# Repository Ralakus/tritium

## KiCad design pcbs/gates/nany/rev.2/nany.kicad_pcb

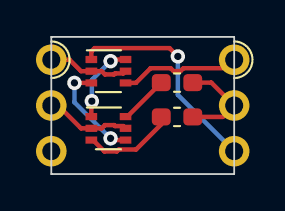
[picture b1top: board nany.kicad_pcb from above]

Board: 2 copper layers, 10.2 x 7.6 mm, 6 parts (0 on the bottom side), 9 nets.

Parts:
J1, J2: Conn_01x03; Edge_Castellation_1x03_P2.54
Q1, Q2: BSS8402DW; SOT-363_SC-70-6
R1, R2: 12k; R_0603_1608Metric_Pad1.05x0.95mm_HandSolder

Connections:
A: J1.1, Q1.2, Q1.5
B: J1.2, Q2.2, Q2.5
unnamed: Q1.3, Q2.4
unnamed: Q1.6, Q2.1
unnamed: Q2.3, R1.1
unnamed: Q2.6, R2.2
Out: J2.2, R1.2, R2.1
Vdd: J2.1, Q1.4
Vss: J2.3, Q1.1

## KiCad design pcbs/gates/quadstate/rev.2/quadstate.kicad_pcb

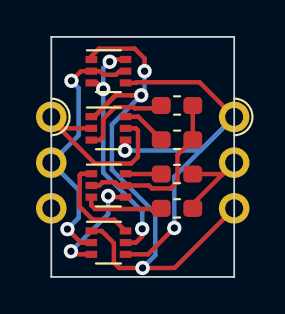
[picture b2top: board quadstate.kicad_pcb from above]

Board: 2 copper layers, 10.2 x 13.3 mm, 10 parts (0 on the bottom side), 13 nets.

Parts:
J1, J2: Conn_01x03; Edge_Castellation_1x03_P2.54
Q1, Q2, Q3, Q4: BSS8402DW; SOT-363_SC-70-6
R1, R2, R3, R4: 12k; R_0603_1608Metric_Pad1.05x0.95mm_HandSolder

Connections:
Gate: J1.2, Q1.2, Q1.5, Q2.2
In: J1.1, Q3.2, Q3.5
unnamed: Q1.3, Q1.6, Q2.5
unnamed: Q2.3, Q4.4
unnamed: Q2.6, Q4.1
unnamed: Q3.3, R1.1
unnamed: Q3.6, R2.2
unnamed: Q4.2, Q4.5, R1.2, R2.1
unnamed: Q4.3, R3.1
unnamed: Q4.6, R4.2
Out: J2.2, R3.2, R4.1
Vdd: J2.1, Q1.4, Q2.4, Q3.4
Vss: J2.3, Q1.1, Q2.1, Q3.1

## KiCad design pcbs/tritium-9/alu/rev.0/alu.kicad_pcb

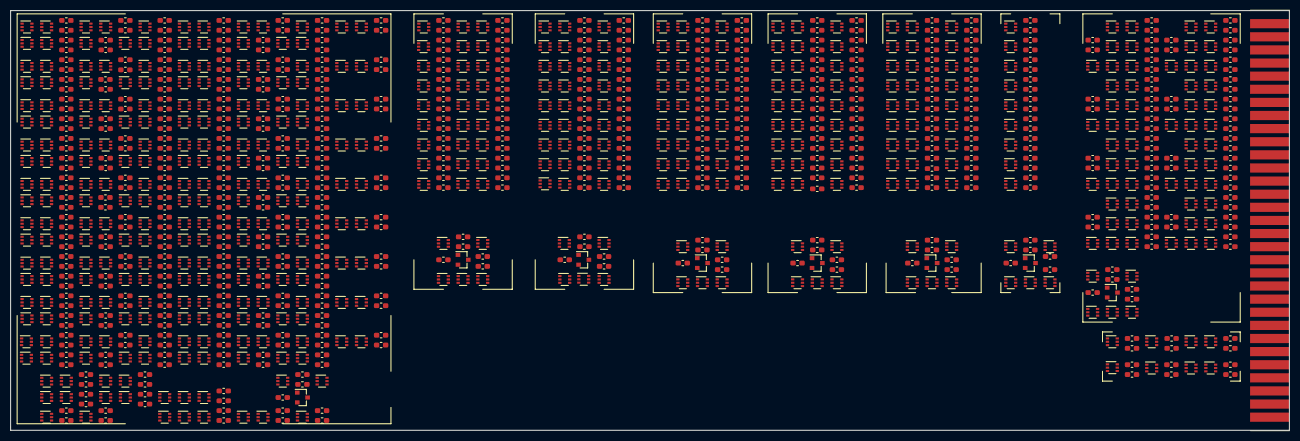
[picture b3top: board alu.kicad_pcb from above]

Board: 2 copper layers, 247.7 x 81.3 mm, 1037 parts (0 on the bottom side), 1030 nets, no tracks yet.

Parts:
J1: Conn_02x31_Top_Bottom; BUS_AT_8bit
Q1, Q2, Q3, Q4, Q5, Q6, Q7, Q8, Q9, Q10, Q11, Q12, Q13, Q14, Q15, Q16, Q17, Q18, Q19, Q20, Q21, Q22, Q23, Q24, Q25, Q26, Q27, Q28, Q29, Q30, Q31, Q32, Q33, Q34, Q35, Q36, Q37, Q38, Q39, Q40, Q41, Q42, Q43, Q44, Q45, Q46, Q47, Q48, Q49, Q50, Q51, Q52, Q53, Q54, Q55, Q56, Q57, Q58, Q59, Q60, Q61, Q62, Q63, Q64, Q65, Q66, Q67, Q68, Q69, Q70, Q71, Q72, Q73, Q74, Q75, Q76, Q77, Q78, Q79, Q80, Q81, Q82, Q83, Q84, Q85, Q86, Q87, Q88, Q89, Q90, Q91, Q92, Q93, Q94, Q95, Q96, Q97, Q98, Q99, Q100, Q101, Q102, Q103, Q104, Q105, Q106, Q107, Q108, Q109, Q110, Q111, Q112, Q113, Q114, Q115, Q116, Q117, Q118, Q119, Q120, Q121, Q122, Q123, Q124, Q125, Q126, Q127, Q128, Q129, Q130, Q131, Q132, Q133, Q134, Q135, Q136, Q137, Q138, Q139, Q140, Q141, Q142, Q143, Q144, Q145, Q146, Q147, Q148, Q149, Q150, Q151, Q152, Q153, Q154, Q155, Q156, Q157, Q158, Q159, Q160, Q161, Q162, Q163, Q164, Q165, Q166, Q167, Q168, Q169, Q170, Q171, Q172, Q173, Q174, Q175, Q176, Q177, Q178, Q179, Q180, Q181, Q182, Q183, Q184, Q185, Q186, Q187, Q188, Q189, Q190, Q191, Q192, Q193, Q194, Q195, Q196, Q197, Q198, Q199, Q200, Q201, Q202, Q203, Q204, Q205, Q206, Q207, Q208, Q209, Q210, Q211, Q212, Q213, Q214, Q215, Q216, Q217, Q218, Q219, Q220, Q221, Q222, Q223, Q224, Q225, Q226, Q227, Q228, Q229, Q230, Q231, Q232, Q233, Q234, Q235, Q236, Q237, Q238, Q239, Q240, Q241, Q242, Q243, Q244, Q245, Q246, Q247, Q248, Q249, Q250, Q251, Q252, Q253, Q254, Q255, Q256, Q257, Q258, Q259, Q260, Q261, Q262, Q263, Q264, Q265, Q266, Q267, Q268, Q269, Q270, Q271, Q272, Q273, Q274, Q275, Q276, Q277, Q278, Q279, Q280, Q281, Q282, Q283, Q284, Q285, Q286, Q287, Q288, Q289, Q290, Q291, Q292, Q293, Q294, Q295, Q296, Q297, Q298, Q299, Q300, Q301, Q302, Q303, Q304, Q305, Q306, Q307, Q308, Q309, Q310, Q311, Q312, Q313, Q314, Q315, Q316, Q317, Q318, Q319, Q320, Q321, Q322, Q323, Q324, Q325, Q326, Q327, Q328, Q329, Q330, Q331, Q332, Q333, Q334, Q335, Q336, Q337, Q338, Q339, Q340, Q341, Q342, Q343, Q344, Q345, Q346, Q347, Q348, Q349, Q350, Q351, Q352, Q353, Q354, Q355, Q356, Q357, Q358, Q359, Q360, Q361, Q362, Q363, Q364, Q365, Q366, Q367, Q368, Q369, Q370, Q371, Q372, Q373, Q374, Q375, Q376, Q377, Q378, Q379, Q380, Q381, Q382, Q383, Q384, Q385, Q386, Q387, Q388, Q389, Q390, Q391, Q392, Q393, Q394, Q395, Q396, Q397, Q398, Q399, Q400, Q401, Q402, Q403, Q404, Q405, Q406, Q407, Q408, Q409, Q410, Q411, Q412, Q413, Q414, Q415, Q416, Q417, Q418, Q419, Q420, Q421, Q422, Q424, Q425, Q426, Q428, Q429, Q430, Q432, Q433, Q434, Q436, Q437, Q438, Q440, Q441, Q442, Q444, Q445, Q446, Q448, Q449, Q450, Q452, Q453, Q454, Q455, Q456, Q457, Q458, Q459, Q460, Q461, Q462, Q463, Q464, Q465, Q466, Q467, Q468, Q469, Q470: BSS8402DW; SOT-363_SC-70-6
Q423, Q427, Q431, Q435, Q439, Q443, Q447, Q451: 2N7002; SOT-23
R2, R3, R4, R5, R6, R7, R8, R9, R10, R11, R12, R13, R14, R15, R16, R17, R18, R19, R20, R21, R22, R23, R24, R25, R26, R27, R28, R29, R30, R31, R32, R33, R34, R35, R36, R37, R38, R39, R40, R41, R42, R43, R44, R45, R46, R47, R48, R49, R50, R51, R52, R53, R54, R55, R56, R57, R58, R59, R60, R61, R62, R63, R64, R65, R66, R67, R68, R69, R70, R71, R72, R73, R74, R75, R76, R77, R78, R79, R80, R81, R82, R83, R84, R85, R86, R87, R88, R89, R90, R91, R92, R93, R94, R95, R96, R97, R98, R99, R100, R101, R102, R103, R104, R105, R106, R107, R108, R109, R110, R111, R112, R113, R114, R115, R116, R117, R118, R119, R120, R121, R122, R123, R124, R125, R126, R127, R128, R129, R130, R131, R132, R133, R134, R135, R136, R137, R138, R139, R140, R141, R142, R143, R144, R145, R146, R147, R148, R149, R150, R151, R152, R153, R154, R155, R156, R157, R158, R159, R160, R161, R162, R163, R164, R165, R166, R167, R168, R169, R170, R171, R172, R173, R174, R175, R176, R177, R178, R179, R180, R181, R182, R183, R184, R185, R186, R187, R188, R189, R190, R191, R192, R193, R194, R195, R196, R197, R198, R199, R200, R201, R202, R203, R204, R205, R206, R207, R208, R209, R210, R211, R212, R213, R214, R215, R216, R217, R218, R219, R220, R221, R222, R223, R224, R225, R226, R227, R228, R229, R230, R231, R232, R233, R234, R235, R236, R237, R238, R239, R240, R241, R242, R243, R244, R245, R246, R247, R248, R249, R250, R251, R252, R253, R254, R255, R256, R257, R258, R259, R260, R261, R262, R263, R264, R265, R266, R267, R268, R269, R270, R271, R272, R273, R274, R275, R276, R277, R278, R279, R280, R281, R282, R283, R284, R285, R286, R287, R288, R289, R290, R291, R292, R293, R294, R295, R296, R297, R298, R299, R300, R301, R302, R303, R304, R305, R306, R307, R308, R309, R310, R311, R312, R313, R314, R315, R316, R317, R318, R319, R320, R321, R322, R323, R324, R325, R326, R327, R328, R329, R330, R331, R332, R333, R334, R335, R336, R337, R338, R339, R340, R341, R342, R343, R344, R345, R346, R347, R348, R349, R350, R351, R352, R353, R354, R355, R356, R357, R358, R359, R360, R361, R362, R363, R364, R365, R366, R367, R368, R369, R370, R371, R372, R373, R374, R375, R376, R377, R378, R379, R380, R381, R382, R383, R384, R385, R386, R387, R388, R389, R390, R391, R392, R393, R394, R395, R396, R397, R398, R399, R400, R401, R402, R403, R404, R405, R406, R407, R408, R409, R410, R411, R412, R413, R414, R415, R416, R417, R418, R419, R420, R421, R422, R423, R424, R425, R426, R427, R428, R429, R430, R431, R432, R433, R434, R435, R436, R437, R438, R439, R440, R441, R442, R443, R444, R445, R446, R447, R448, R449, R450, R451, R452, R453, R454, R455, R456, R457, R458, R459, R460, R461, R462, R463, R464, R465, R466, R467, R468, R469, R470, R471, R472, R473, R474, R475, R476, R477, R478, R479, R480, R481, R482, R483, R484, R485, R486, R487, R488, R489, R490, R491, R492, R493, R494, R495, R496, R497, R498, R499, R500, R501, R502, R503, R504, R505, R506, R507, R508, R517, R518, R519, R520, R521, R522, R523, R524, R525, R526, R527, R528, R529, R530, R531, R532, R533, R534, R535, R536, R537, R538, R539, R540, R541, R542, R543, R544, R545, R546, R547, R548, R549, R550, R551, R552, R553, R554, R555, R556, R557, R558, R560, R561, R562, R563, R564, R565, R566, R567, R568, R569, R570, R571, R572, R573, R574, R575: 12k; R_0603_1608Metric_Pad1.05x0.95mm_HandSolder
R559: 470k; R_0603_1608Metric_Pad1.05x0.95mm_HandSolder

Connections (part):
/FnA0: Q5.6, Q417.2, Q417.5, Q454.2, Q454.5, Q456.2, Q456.5, Q458.2, Q458.5, R439.1
/FnA1: Q460.2, Q460.5, Q462.2, Q462.5, Q464.2, Q464.5, R528.1, R529.2
/FnA2: Q412.2, Q412.5, Q466.2, Q466.5, Q468.2, Q468.5, Q470.2, Q470.5, R452.1, R517.2
/FnB0: Q4.6, Q416.2, Q416.5, Q421.2, Q421.5, Q433.2, Q433.5, Q445.2, Q445.5, R5.1
/FnB1: Q425.2, Q425.5, Q437.2, Q437.5, Q449.2, Q449.5, R526.1, R527.2
/FnB2: Q411.2, Q411.5, Q429.2, Q429.5, Q441.2, Q441.5, Q453.2, Q453.5, R450.1, R451.2
/adder/CarryIn: Q12.2, Q12.5, Q15.2, Q15.5, R530.1, R531.2
/adder/Vdd: Q6.4, Q7.4, Q8.4, Q9.4, Q10.4, Q11.4, Q12.4, Q13.4, Q14.4, Q18.4, Q19.4, Q20.4, Q21.4, Q22.4, Q23.4, Q27.4, Q28.4, Q29.4, Q30.4, Q31.4, Q32.4, Q36.4, Q37.4, Q38.4, Q39.4, Q40.4, Q41.4, Q42.4, Q43.4, Q44.4, Q48.4, Q49.4, Q50.4, Q51.4, Q52.4, Q53.4, Q57.4, Q58.4, Q59.4, Q60.4, Q61.4, Q62.4, Q66.4, Q67.4, Q68.4, Q72.4, Q73.4, Q74.4, Q75.4, Q76.4, Q77.4, Q78.4, Q79.4, Q80.4, Q84.4, Q85.4, Q86.4, Q87.4, Q88.4, Q89.4, Q93.4, Q94.4, Q95.4, Q96.4, Q97.4, Q98.4, Q102.4, Q103.4, Q104.4, Q105.4, Q106.4, Q107.4, Q108.4, Q109.4, Q110.4, Q114.4, Q115.4, Q116.4, Q117.4, Q118.4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
/adder/Vss: Q6.1, Q7.1, Q8.1, Q9.1, Q10.1, Q11.1, Q12.1, Q13.1, Q14.1, Q18.1, Q19.1, Q20.1, Q21.1, Q22.1, Q23.1, Q27.1, Q28.1, Q29.1, Q30.1, Q31.1, Q32.1, Q36.1, Q37.1, Q38.1, Q39.1, Q40.1, Q41.1, Q42.1, Q43.1, Q44.1, Q48.1, Q49.1, Q50.1, Q51.1, Q52.1, Q53.1, Q57.1, Q58.1, Q59.1, Q60.1, Q61.1, Q62.1, Q66.1, Q67.1, Q68.1, Q72.1, Q73.1, Q74.1, Q75.1, Q76.1, Q77.1, Q78.1, Q79.1, Q80.1, Q84.1, Q85.1, Q86.1, Q87.1, Q88.1, Q89.1, Q93.1, Q94.1, Q95.1, Q96.1, Q97.1, Q98.1, Q102.1, Q103.1, Q104.1, Q105.1, Q106.1, Q107.1, Q108.1, Q109.1, Q110.1, Q114.1, Q115.1, Q116.1, Q117.1, Q118.1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
/any/Vdd: Q312.4, Q314.4, Q315.4, Q317.4, Q318.4, Q320.4, Q321.4, Q323.4, Q324.4, Q326.4, Q327.4, Q329.4, Q330.4, Q332.4, Q333.4, Q335.4, Q336.4, Q338.4, Q442.3
/any/Vss: Q312.1, Q314.1, Q315.1, Q317.1, Q318.1, Q320.1, Q321.1, Q323.1, Q324.1, Q326.1, Q327.1, Q329.1, Q330.1, Q332.1, Q333.1, Q335.1, Q336.1, Q338.1, Q442.6
/compare/Vdd: Q258.4, Q259.4, Q260.4, Q261.4, Q262.4, Q263.4, Q264.4, Q265.4, Q266.4, Q267.4, Q268.4, Q269.4, Q270.4, Q271.4, Q272.4, Q273.4, Q274.4, Q275.4, Q276.4, Q277.4, Q278.4, Q279.4, Q280.4, Q281.4, Q282.4, Q283.4, Q284.4, Q426.3
/compare/Vss: Q258.1, Q259.1, Q260.1, Q261.1, Q262.1, Q263.1, Q264.1, Q265.1, Q266.1, Q267.1, Q268.1, Q269.1, Q270.1, Q271.1, Q272.1, Q273.1, Q274.1, Q275.1, Q276.1, Q277.1, Q278.1, Q279.1, Q280.1, Q281.1, Q282.1, Q283.1, Q284.1, Q426.6
/consensus/Vdd: Q285.4, Q286.4, Q287.4, Q288.4, Q289.4, Q290.4, Q291.4, Q292.4, Q293.4, Q294.4, Q295.4, Q296.4, Q297.4, Q298.4, Q299.4, Q300.4, Q301.4, Q302.4, Q303.4, Q304.4, Q305.4, Q306.4, Q307.4, Q308.4, Q309.4, Q310.4, Q311.4, Q438.3
/consensus/Vss: Q285.1, Q286.1, Q287.1, Q288.1, Q289.1, Q290.1, Q291.1, Q292.1, Q293.1, Q294.1, Q295.1, Q296.1, Q297.1, Q298.1, Q299.1, Q300.1, Q301.1, Q302.1, Q303.1, Q304.1, Q305.1, Q306.1, Q307.1, Q308.1, Q309.1, Q310.1, Q311.1, Q438.6
/inverter/Vdd: Q339.4, Q340.4, Q341.4, Q342.4, Q343.4, Q344.4, Q345.4, Q346.4, Q347.4, Q446.3
/inverter/Vss: Q339.1, Q340.1, Q341.1, Q342.1, Q343.1, Q344.1, Q345.1, Q346.1, Q347.1, Q446.6
/max/Vdd: Q231.4, Q233.4, Q234.4, Q236.4, Q237.4, Q239.4, Q240.4, Q242.4, Q243.4, Q245.4, Q246.4, Q248.4, Q249.4, Q251.4, Q252.4, Q254.4, Q255.4, Q257.4, Q434.3
/max/Vss: Q231.1, Q232.1, Q233.1, Q234.1, Q235.1, Q236.1, Q237.1, Q238.1, Q239.1, Q240.1, Q241.1, Q242.1, Q243.1, Q244.1, Q245.1, Q246.1, Q247.1, Q248.1, Q249.1, Q250.1, Q251.1, Q252.1, Q253.1, Q254.1, Q255.1, Q256.1, Q257.1, Q434.6
/min/Vdd: Q204.4, Q205.4, Q206.4, Q207.4, Q208.4, Q209.4, Q210.4, Q211.4, Q212.4, Q213.4, Q214.4, Q215.4, Q216.4, Q217.4, Q218.4, Q219.4, Q220.4, Q221.4, Q222.4, Q223.4, Q224.4, Q225.4, Q226.4, Q227.4, Q228.4, Q229.4, Q230.4, Q430.3
/min/Vss: Q204.1, Q206.1, Q207.1, Q209.1, Q210.1, Q212.1, Q213.1, Q215.1, Q216.1, Q218.1, Q219.1, Q221.1, Q222.1, Q224.1, Q225.1, Q227.1, Q228.1, Q230.1, Q430.6
/sign/Vdd: Q351.4, Q352.4, Q353.4, Q354.4, Q356.4, Q357.4, Q358.4, Q359.4, Q360.4, Q361.4, Q362.4, Q363.4, Q365.4, Q366.4, Q367.4, Q368.4, Q373.4, Q374.4, Q375.4, Q376.4, Q381.4, Q382.4, Q383.4, Q384.4, Q385.4, Q386.4, Q387.4, Q388.4, Q391.4, Q392.4, Q395.4, Q396.4, Q397.4, Q398.4, Q400.4, Q402.4, Q403.4, Q404.4, Q405.4, Q407.4, Q450.3
/sign/Vss: Q351.1, Q352.1, Q353.1, Q354.1, Q356.1, Q357.1, Q358.1, Q359.1, Q360.1, Q361.1, Q362.1, Q363.1, Q365.1, Q366.1, Q367.1, Q368.1, Q373.1, Q374.1, Q375.1, Q376.1, Q381.1, Q382.1, Q383.1, Q384.1, Q385.1, Q386.1, Q387.1, Q388.1, Q391.1, Q392.1, Q395.1, Q396.1, Q397.1, Q398.1, Q400.1, Q402.1, Q403.1, Q404.1, Q405.1, Q407.1, Q450.6
A0: J1.40, Q6.2, Q6.5, Q7.2, Q7.5, Q230.2, Q230.5, Q257.2, Q257.5, Q283.2, Q283.5, Q311.2, Q311.5, Q338.2, Q338.5, Q347.2, Q347.5, Q402.2, Q402.5, Q406.2, Q406.5
A1: J1.39, Q72.2, Q72.5, Q73.2, Q73.5, Q227.2, Q227.5, Q254.2, Q254.5, Q280.2, Q280.5, Q308.2, Q308.5, Q335.2, Q335.5, Q346.2, Q346.5, Q354.2, Q354.5, Q372.2, Q372.5
A2: J1.38, Q138.2, Q138.5, Q139.2, Q139.5, Q224.2, Q224.5, Q251.2, Q251.5, Q277.2, Q277.5, Q305.2, Q305.5, Q332.2, Q332.5, Q345.2, Q345.5, Q362.2, Q362.5, Q368.2, Q368.5
A3: J1.37, Q8.2, Q8.5, Q9.2, Q9.5, Q221.2, Q221.5, Q248.2, Q248.5, Q274.2, Q274.5, Q302.2, Q302.5, Q329.2, Q329.5, Q344.2, Q344.5, Q353.2, Q353.5, Q371.2, Q371.5
A4: J1.36, Q74.2, Q74.5, Q75.2, Q75.5, Q218.2, Q218.5, Q245.2, Q245.5, Q271.2, Q271.5, Q299.2, Q299.5, Q326.2, Q326.5, Q343.2, Q343.5, Q360.2, Q360.5, Q367.2, Q367.5
A5: J1.35, Q140.2, Q140.5, Q141.2, Q141.5, Q215.2, Q215.5, Q242.2, Q242.5, Q268.2, Q268.5, Q296.2, Q296.5, Q323.2, Q323.5, Q342.2, Q342.5, Q352.2, Q352.5, Q370.2, Q370.5
A6: J1.34, Q10.2, Q10.5, Q11.2, Q11.5, Q212.2, Q212.5, Q239.2, Q239.5, Q265.2, Q265.5, Q293.2, Q293.5, Q320.2, Q320.5, Q341.2, Q341.5, Q358.2, Q358.5, Q366.2, Q366.5
A7: J1.33, Q76.2, Q76.5, Q77.2, Q77.5, Q209.2, Q209.5, Q236.2, Q236.5, Q262.2, Q262.5, Q290.2, Q290.5, Q317.2, Q317.5, Q340.2, Q340.5, Q351.2, Q351.5, Q369.2, Q369.5
A8: J1.32, Q142.2, Q142.5, Q143.2, Q143.5, Q206.2, Q206.5, Q233.2, Q233.5, Q259.2, Q259.5, Q287.2, Q287.5, Q314.2, Q314.5, Q339.2, Q339.5, Q356.2, Q356.5, Q365.2, Q365.5
B0: J1.49, Q36.2, Q36.5, Q37.2, Q37.5, Q229.2, Q229.5, Q256.2, Q256.5, Q284.2, Q284.5, Q310.2, Q310.5, Q337.2, Q337.5
B1: J1.48, Q102.2, Q102.5, Q103.2, Q103.5, Q226.2, Q226.5, Q253.2, Q253.5, Q281.2, Q281.5, Q307.2, Q307.5, Q334.2, Q334.5
B2: J1.47, Q168.2, Q168.5, Q169.2, Q169.5, Q223.2, Q223.5, Q250.2, Q250.5, Q278.2, Q278.5, Q304.2, Q304.5, Q331.2, Q331.5
B3: J1.46, Q38.2, Q38.5, Q39.2, Q39.5, Q220.2, Q220.5, Q247.2, Q247.5, Q275.2, Q275.5, Q301.2, Q301.5, Q328.2, Q328.5
B4: J1.45, Q104.2, Q104.5, Q105.2, Q105.5, Q217.2, Q217.5, Q244.2, Q244.5, Q272.2, Q272.5, Q298.2, Q298.5, Q325.2, Q325.5
B5: J1.44, Q170.2, Q170.5, Q171.2, Q171.5, Q214.2, Q214.5, Q241.2, Q241.5, Q269.2, Q269.5, Q295.2, Q295.5, Q322.2, Q322.5
B6: J1.43, Q40.2, Q40.5, Q41.2, Q41.5, Q211.2, Q211.5, Q238.2, Q238.5, Q266.2, Q266.5, Q292.2, Q292.5, Q319.2, Q319.5
B7: J1.42, Q106.2, Q106.5, Q107.2, Q107.5, Q208.2, Q208.5, Q235.2, Q235.5, Q263.2, Q263.5, Q289.2, Q289.5, Q316.2, Q316.5
B8: J1.41, Q172.2, Q172.5, Q173.2, Q173.5, Q205.2, Q205.5, Q232.2, Q232.5, Q260.2, Q260.5, Q286.2, Q286.5, Q313.2, Q313.5
CarryIn: J1.30, Q3.2, Q3.5, Q355.2, Q355.5
CarryOut: J1.31, R239.1, R240.2
Fn0: J1.58, Q4.2, Q4.5
Fn1: J1.57, Q5.2, Q5.5
GND: J1.20, J1.51, Q1.5, Q423.2, Q427.2, Q431.2, Q435.2, Q439.2, Q443.2, Q447.2, Q451.2, R559.1
unnamed: Q1.2, Q414.2, Q414.5, R535.1, R536.2
unnamed: Q1.3, Q1.6, R558.1
unnamed: Q1.4, Q2.2, Q2.5, R559.2
unnamed: Q2.3, R2.2
unnamed: Q2.6, R3.1
unnamed: Q3.3, Q348.3, R440.2
unnamed: Q3.6, Q348.1
unnamed: Q10.3, Q17.4
unnamed: Q10.6, Q17.1
unnamed: Q11.3, Q14.3, R11.2
unnamed: Q11.6, Q14.6, R12.1
unnamed: Q7.3, Q12.3, R7.2
unnamed: Q7.6, Q12.6, R8.1
unnamed: Q13.2, Q13.5, Q16.2, Q16.5, R235.1, R236.2
unnamed: Q9.3, Q13.3, R9.2
unnamed: Q9.6, Q13.6, R10.1
unnamed: Q14.2, Q14.5, Q17.2, Q17.5, R237.1, R238.2
unnamed: Q6.6, Q15.1
unnamed: Q15.3, R13.2
unnamed: Q6.3, Q15.4
unnamed: Q15.6, R14.1
unnamed: Q8.6, Q16.1
unnamed: Q16.3, R15.2
unnamed: Q8.3, Q16.4
unnamed: Q16.6, R16.1
unnamed: Q17.3, R17.2
unnamed: Q17.6, R18.1
unnamed: Q18.2, Q18.5, Q69.2, Q69.5, R7.1, R8.2
unnamed: Q18.3, R19.2
unnamed: Q18.6, R20.1
unnamed: Q19.2, Q19.5, Q70.2, Q70.5, R9.1, R10.2
unnamed: Q19.3, R21.2
unnamed: Q19.6, R22.1
unnamed: Q20.2, Q20.5, Q71.2, Q71.5, R11.1, R12.2
unnamed: Q20.3, R23.2
unnamed: Q20.6, R24.1
unnamed: Q21.2, Q21.5, R13.1, R14.2
unnamed: Q21.3, Q24.4
unnamed: Q21.6, Q24.1
unnamed: Q22.2, Q22.5, R15.1, R16.2
unnamed: Q22.3, Q25.4
unnamed: Q22.6, Q25.1
unnamed: Q23.2, Q23.5, R17.1, R18.2
unnamed: Q23.3, Q26.4
unnamed: Q23.6, Q26.1
unnamed: Q24.2, Q24.5, Q33.2, Q33.5, R19.1, R20.2
unnamed: Q24.3, R25.2
unnamed: Q24.6, R26.1
unnamed: Q25.2, Q25.5, Q34.2, Q34.5, R21.1, R22.2
unnamed: Q25.3, R27.2
unnamed: Q25.6, R28.1
unnamed: Q26.2, Q26.5, Q35.2, Q35.5, R23.1, R24.2
unnamed: Q26.3, R29.2
unnamed: Q26.6, R30.1
unnamed: Q27.2, Q27.5, R25.1, R26.2
unnamed: Q27.3, R31.2
unnamed: Q27.6, R32.1
unnamed: Q28.2, Q28.5, R27.1, R28.2
unnamed: Q28.3, R33.2
unnamed: Q28.6, R34.1
unnamed: Q29.2, Q29.5, R29.1, R30.2
unnamed: Q29.3, R35.2
unnamed: Q29.6, R36.1
unnamed: Q30.2, Q30.5, R31.1, R32.2
unnamed: Q30.3, Q33.4
unnamed: Q30.6, Q33.1
unnamed: Q31.2, Q31.5, R33.1, R34.2
unnamed: Q31.3, Q34.4
unnamed: Q31.6, Q34.1
unnamed: Q32.2, Q32.5, R35.1, R36.2
unnamed: Q32.3, Q35.4
unnamed: Q32.6, Q35.1
unnamed: Q33.3, R37.2
unnamed: Q33.6, R38.1
unnamed: Q34.3, R39.2
unnamed: Q34.6, R40.1
unnamed: Q35.3, R41.2
unnamed: Q35.6, R42.1
unnamed: Q36.3, Q45.4
unnamed: Q36.6, Q45.1
unnamed: Q37.3, Q42.3, R43.2
unnamed: Q37.6, Q42.6, R44.1
unnamed: Q38.3, Q46.4
unnamed: Q38.6, Q46.1
unnamed: Q39.3, Q43.3, R45.2
unnamed: Q39.6, Q43.6, R46.1
unnamed: Q40.3, Q47.4
unnamed: Q40.6, Q47.1
unnamed: Q41.3, Q44.3, R47.2
unnamed: Q41.6, Q44.6, R48.1
unnamed: Q42.2, Q42.5, Q45.2, Q45.5, R37.1, R38.2
unnamed: Q43.2, Q43.5, Q46.2, Q46.5, R39.1, R40.2
unnamed: Q44.2, Q44.5, Q47.2, Q47.5, R41.1, R42.2
unnamed: Q45.3, R49.2
unnamed: Q45.6, R50.1
unnamed: Q46.3, R51.2
unnamed: Q46.6, R52.1
unnamed: Q47.3, R53.2
unnamed: Q47.6, R54.1
unnamed: Q48.2, Q48.5, Q66.2, Q66.5, R43.1, R44.2
unnamed: Q48.3, R55.2
unnamed: Q48.6, R56.1
unnamed: Q49.2, Q49.5, Q67.2, Q67.5, R45.1, R46.2
unnamed: Q49.3, R57.2
unnamed: Q49.6, R58.1
unnamed: Q50.2, Q50.5, Q68.2, Q68.5, R47.1, R48.2
unnamed: Q50.3, R59.2
unnamed: Q50.6, R60.1
unnamed: Q51.2, Q51.5, R49.1, R50.2
unnamed: Q51.3, Q54.4
unnamed: Q51.6, Q54.1
unnamed: Q52.2, Q52.5, R51.1, R52.2
unnamed: Q52.3, Q55.4
unnamed: Q52.6, Q55.1
unnamed: Q53.2, Q53.5, R53.1, R54.2
unnamed: Q53.3, Q56.4
unnamed: Q53.6, Q56.1
unnamed: Q54.2, Q54.5, Q63.2, Q63.5, R55.1, R56.2
unnamed: Q54.3, R61.2
unnamed: Q54.6, R62.1
unnamed: Q55.2, Q55.5, Q64.2, Q64.5, R57.1, R58.2
unnamed: Q55.3, R63.2
unnamed: Q55.6, R64.1
unnamed: Q56.2, Q56.5, Q65.2, Q65.5, R59.1, R60.2
unnamed: Q56.3, R65.2
unnamed: Q56.6, R66.1
unnamed: Q57.2, Q57.5, R61.1, R62.2
unnamed: Q57.3, R67.2
unnamed: Q57.6, R68.1
unnamed: Q58.2, Q58.5, R63.1, R64.2
unnamed: Q58.3, R69.2
unnamed: Q58.6, R70.1
unnamed: Q59.2, Q59.5, R65.1, R66.2
unnamed: Q59.3, R71.2
unnamed: Q59.6, R72.1
unnamed: Q60.2, Q60.5, R67.1, R68.2
unnamed: Q60.3, Q63.4
unnamed: Q60.6, Q63.1
unnamed: Q61.2, Q61.5, R69.1, R70.2
unnamed: Q61.3, Q64.4
unnamed: Q61.6, Q64.1
unnamed: Q62.2, Q62.5, R71.1, R72.2
unnamed: Q62.3, Q65.4
unnamed: Q62.6, Q65.1
unnamed: Q63.3, R73.2
unnamed: Q63.6, R74.1
unnamed: Q64.3, R75.2
unnamed: Q64.6, R76.1
unnamed: Q65.3, R77.2
unnamed: Q65.6, R78.1
unnamed: Q66.3, Q69.4
unnamed: Q66.6, Q69.1
unnamed: Q67.3, Q70.4
unnamed: Q67.6, Q70.1
unnamed: Q68.3, Q71.4
unnamed: Q68.6, Q71.1
unnamed: Q69.3, R79.2
unnamed: Q69.6, R80.1
unnamed: Q70.3, R81.2
unnamed: Q70.6, R82.1
unnamed: Q71.3, R83.2
unnamed: Q71.6, R84.1
unnamed: Q72.3, Q81.4
unnamed: Q72.6, Q81.1
unnamed: Q73.3, Q78.3, R85.2
unnamed: Q73.6, Q78.6, R86.1
unnamed: Q74.3, Q82.4
unnamed: Q74.6, Q82.1
unnamed: Q75.3, Q79.3, R87.2
unnamed: Q75.6, Q79.6, R88.1
unnamed: Q76.3, Q83.4
unnamed: Q76.6, Q83.1
unnamed: Q77.3, Q80.3, R89.2
unnamed: Q77.6, Q80.6, R90.1
unnamed: Q78.2, Q78.5, Q81.2, Q81.5, R79.1, R80.2
unnamed: Q79.2, Q79.5, Q82.2, Q82.5, R81.1, R82.2
unnamed: Q80.2, Q80.5, Q83.2, Q83.5, R83.1, R84.2
unnamed: Q81.3, R91.2
unnamed: Q81.6, R92.1
unnamed: Q82.3, R93.2
unnamed: Q82.6, R94.1
unnamed: Q83.3, R95.2
unnamed: Q83.6, R96.1
unnamed: Q84.3, R97.2
unnamed: Q84.6, R98.1
unnamed: Q85.3, R99.2
unnamed: Q85.6, R100.1
unnamed: Q86.3, R101.2
unnamed: Q86.6, R102.1
unnamed: Q87.2, Q87.5, R91.1, R92.2
unnamed: Q87.3, Q90.4
unnamed: Q87.6, Q90.1
unnamed: Q88.2, Q88.5, R93.1, R94.2
unnamed: Q88.3, Q91.4
unnamed: Q88.6, Q91.1
unnamed: Q89.2, Q89.5, R95.1, R96.2
unnamed: Q89.3, Q92.4
unnamed: Q89.6, Q92.1
unnamed: Q90.2, Q90.5, Q99.2, Q99.5, R97.1, R98.2
unnamed: Q90.3, R103.2
unnamed: Q90.6, R104.1
unnamed: Q91.3, R105.2
unnamed: Q91.6, R106.1
unnamed: Q92.3, R107.2
unnamed: Q92.6, R108.1
unnamed: Q93.2, Q93.5, R103.1, R104.2
unnamed: Q93.3, R109.2
unnamed: Q93.6, R110.1
unnamed: Q94.2, Q94.5, R105.1, R106.2
unnamed: Q94.3, R111.2
unnamed: Q94.6, R112.1
unnamed: Q95.2, Q95.5, R107.1, R108.2
unnamed: Q95.3, R113.2
unnamed: Q95.6, R114.1
unnamed: Q96.2, Q96.5, R109.1, R110.2
unnamed: Q96.3, Q99.4
unnamed: Q96.6, Q99.1
unnamed: Q97.2, Q97.5, R111.1, R112.2
unnamed: Q98.2, Q98.5, R113.1, R114.2
unnamed: Q99.3, R115.2
unnamed: Q99.6, R116.1
unnamed: Q97.6, Q100.1
unnamed: Q91.2, Q91.5, Q100.2, Q100.5, R99.1, R100.2
unnamed: Q100.3, R117.2
unnamed: Q97.3, Q100.4
unnamed: Q100.6, R118.1
unnamed: Q98.6, Q101.1
unnamed: Q92.2, Q92.5, Q101.2, Q101.5, R101.1, R102.2
unnamed: Q101.3, R119.2
unnamed: Q98.3, Q101.4
unnamed: Q101.6, R120.1
unnamed: Q102.3, Q111.4
unnamed: Q102.6, Q111.1
unnamed: Q103.3, Q108.3, R121.2
unnamed: Q103.6, Q108.6, R122.1
unnamed: Q104.3, Q112.4
unnamed: Q104.6, Q112.1
unnamed: Q105.3, Q109.3, R123.2
unnamed: Q105.6, Q109.6, R124.1
unnamed: Q106.3, Q113.4
unnamed: Q106.6, Q113.1
unnamed: Q107.3, Q110.3, R125.2
unnamed: Q107.6, Q110.6, R126.1
unnamed: Q108.2, Q108.5, Q111.2, Q111.5, R115.1, R116.2
unnamed: Q109.2, Q109.5, Q112.2, Q112.5, R117.1, R118.2
unnamed: Q110.2, Q110.5, Q113.2, Q113.5, R119.1, R120.2
unnamed: Q111.3, R127.2
unnamed: Q111.6, R128.1
unnamed: Q112.3, R129.2
unnamed: Q112.6, R130.1
unnamed: Q113.3, R131.2
unnamed: Q113.6, R132.1
unnamed: Q114.2, Q114.5, Q132.2, Q132.5, R121.1, R122.2
unnamed: Q114.3, R133.2
unnamed: Q114.6, R134.1
unnamed: Q115.2, Q115.5, Q133.2, Q133.5, R123.1, R124.2
unnamed: Q115.3, R135.2
unnamed: Q115.6, R136.1
unnamed: Q116.2, Q116.5, Q134.2, Q134.5, R125.1, R126.2
unnamed: Q116.3, R137.2
unnamed: Q116.6, R138.1
unnamed: Q117.2, Q117.5, R127.1, R128.2
unnamed: Q117.3, Q120.4
unnamed: Q117.6, Q120.1
unnamed: Q118.2, Q118.5, R129.1, R130.2
unnamed: Q118.3, Q121.4
unnamed: Q118.6, Q121.1
unnamed: Q119.2, Q119.5, R131.1, R132.2
unnamed: Q119.3, Q122.4
unnamed: Q119.6, Q122.1
unnamed: Q120.2, Q120.5, Q129.2, Q129.5, R133.1, R134.2
unnamed: Q120.3, R139.2
unnamed: Q120.6, R140.1
unnamed: Q121.2, Q121.5, Q130.2, Q130.5, R135.1, R136.2
unnamed: Q121.3, R141.2
unnamed: Q121.6, R142.1
unnamed: Q122.2, Q122.5, Q131.2, Q131.5, R137.1, R138.2
unnamed: Q122.3, R143.2
unnamed: Q122.6, R144.1
unnamed: Q123.2, Q123.5, R139.1, R140.2
unnamed: Q123.3, R145.2
unnamed: Q123.6, R146.1
unnamed: Q124.2, Q124.5, R141.1, R142.2
unnamed: Q124.3, R147.2
unnamed: Q124.6, R148.1
unnamed: Q125.2, Q125.5, R143.1, R144.2
unnamed: Q125.3, R149.2
unnamed: Q125.6, R150.1
unnamed: Q126.2, Q126.5, R145.1, R146.2
unnamed: Q126.3, Q129.4
unnamed: Q126.6, Q129.1
unnamed: Q127.2, Q127.5, R147.1, R148.2
unnamed: Q127.3, Q130.4
unnamed: Q127.6, Q130.1
unnamed: Q128.2, Q128.5, R149.1, R150.2
unnamed: Q128.3, Q131.4
unnamed: Q128.6, Q131.1
unnamed: Q129.3, R151.2
unnamed: Q129.6, R152.1
unnamed: Q130.3, R153.2
unnamed: Q130.6, R154.1
unnamed: Q131.3, R155.2
unnamed: Q131.6, R156.1
unnamed: Q132.3, Q135.4
unnamed: Q132.6, Q135.1
unnamed: Q133.3, Q136.4
unnamed: Q133.6, Q136.1
unnamed: Q134.3, Q137.4
unnamed: Q134.6, Q137.1
unnamed: Q84.2, Q84.5, Q135.2, Q135.5, R85.1, R86.2
unnamed: Q135.3, R157.2
unnamed: Q135.6, R158.1
unnamed: Q85.2, Q85.5, Q136.2, Q136.5, R87.1, R88.2
unnamed: Q136.3, R159.2
unnamed: Q136.6, R160.1
unnamed: Q86.2, Q86.5, Q137.2, Q137.5, R89.1, R90.2
unnamed: Q137.3, R161.2
unnamed: Q137.6, R162.1
unnamed: Q138.3, Q147.4
unnamed: Q138.6, Q147.1
unnamed: Q139.3, Q144.3, R163.2
unnamed: Q139.6, Q144.6, R164.1
unnamed: Q140.3, Q148.4
unnamed: Q140.6, Q148.1
unnamed: Q141.3, Q145.3, R165.2
unnamed: Q141.6, Q145.6, R166.1
unnamed: Q142.3, Q149.4
unnamed: Q142.6, Q149.1
unnamed: Q143.3, Q146.3, R167.2
unnamed: Q143.6, Q146.6, R168.1
unnamed: Q144.2, Q144.5, Q147.2, Q147.5, R157.1, R158.2
unnamed: Q145.2, Q145.5, Q148.2, Q148.5, R159.1, R160.2
unnamed: Q146.2, Q146.5, Q149.2, Q149.5, R161.1, R162.2
unnamed: Q147.3, R169.2
unnamed: Q147.6, R170.1
unnamed: Q148.3, R171.2
unnamed: Q148.6, R172.1
unnamed: Q149.3, R173.2
unnamed: Q149.6, R174.1
unnamed: Q150.2, Q150.5, Q201.2, Q201.5, R163.1, R164.2
unnamed: Q150.3, R175.2
unnamed: Q150.6, R176.1
unnamed: Q151.2, Q151.5, Q202.2, Q202.5, R165.1, R166.2
unnamed: Q151.3, R177.2
unnamed: Q151.6, R178.1
unnamed: Q152.2, Q152.5, Q203.2, Q203.5, R167.1, R168.2
unnamed: Q152.3, R179.2
unnamed: Q152.6, R180.1
unnamed: Q153.2, Q153.5, R169.1, R170.2
unnamed: Q153.3, Q156.4
unnamed: Q153.6, Q156.1
unnamed: Q154.2, Q154.5, R171.1, R172.2
unnamed: Q154.3, Q157.4
unnamed: Q154.6, Q157.1
unnamed: Q155.2, Q155.5, R173.1, R174.2
unnamed: Q155.3, Q158.4
unnamed: Q155.6, Q158.1
unnamed: Q156.2, Q156.5, Q165.2, Q165.5, R175.1, R176.2
unnamed: Q156.3, R181.2
unnamed: Q156.6, R182.1
unnamed: Q157.2, Q157.5, Q166.2, Q166.5, R177.1, R178.2
unnamed: Q157.3, R183.2
unnamed: Q157.6, R184.1
unnamed: Q158.2, Q158.5, Q167.2, Q167.5, R179.1, R180.2
unnamed: Q158.3, R185.2
unnamed: Q158.6, R186.1
unnamed: Q159.2, Q159.5, R181.1, R182.2
unnamed: Q159.3, R187.2
unnamed: Q159.6, R188.1
unnamed: Q160.2, Q160.5, R183.1, R184.2
unnamed: Q160.3, R189.2
unnamed: Q160.6, R190.1
unnamed: Q161.2, Q161.5, R185.1, R186.2
unnamed: Q161.3, R191.2
unnamed: Q161.6, R192.1
unnamed: Q162.2, Q162.5, R187.1, R188.2
unnamed: Q162.3, Q165.4
unnamed: Q162.6, Q165.1
unnamed: Q163.2, Q163.5, R189.1, R190.2
unnamed: Q163.3, Q166.4
unnamed: Q163.6, Q166.1
unnamed: Q164.2, Q164.5, R191.1, R192.2
unnamed: Q164.3, Q167.4
unnamed: Q164.6, Q167.1
unnamed: Q165.3, R193.2
unnamed: Q165.6, R194.1
unnamed: Q166.3, R195.2
unnamed: Q166.6, R196.1
unnamed: Q167.3, R197.2
unnamed: Q167.6, R198.1
unnamed: Q168.3, Q177.4
unnamed: Q168.6, Q177.1
unnamed: Q169.3, Q174.3, R199.2
unnamed: Q169.6, Q174.6, R200.1
unnamed: Q170.3, Q178.4
unnamed: Q170.6, Q178.1
unnamed: Q171.3, Q175.3, R201.2
unnamed: Q171.6, Q175.6, R202.1
unnamed: Q172.3, Q179.4
unnamed: Q172.6, Q179.1
unnamed: Q173.3, Q176.3, R203.2
unnamed: Q173.6, Q176.6, R204.1
unnamed: Q174.2, Q174.5, Q177.2, Q177.5, R193.1, R194.2
unnamed: Q175.2, Q175.5, Q178.2, Q178.5, R195.1, R196.2
unnamed: Q176.2, Q176.5, Q179.2, Q179.5, R197.1, R198.2
unnamed: Q177.3, R205.2
unnamed: Q177.6, R206.1
unnamed: Q178.3, R207.2
unnamed: Q178.6, R208.1
unnamed: Q179.3, R209.2
unnamed: Q179.6, R210.1
unnamed: Q180.2, Q180.5, Q198.2, Q198.5, R199.1, R200.2
unnamed: Q180.3, R211.2
unnamed: Q180.6, R212.1
unnamed: Q181.2, Q181.5, Q199.2, Q199.5, R201.1, R202.2
unnamed: Q181.3, R213.2
unnamed: Q181.6, R214.1
unnamed: Q182.2, Q182.5, Q200.2, Q200.5, R203.1, R204.2
unnamed: Q182.3, R215.2
unnamed: Q182.6, R216.1
unnamed: Q183.2, Q183.5, R205.1, R206.2
unnamed: Q183.3, Q186.4
unnamed: Q183.6, Q186.1
unnamed: Q184.2, Q184.5, R207.1, R208.2
unnamed: Q184.3, Q187.4
unnamed: Q184.6, Q187.1
unnamed: Q185.2, Q185.5, R209.1, R210.2
unnamed: Q185.3, Q188.4
unnamed: Q185.6, Q188.1
unnamed: Q186.2, Q186.5, Q195.2, Q195.5, R211.1, R212.2
unnamed: Q186.3, R217.2
unnamed: Q186.6, R218.1
unnamed: Q187.2, Q187.5, Q196.2, Q196.5, R213.1, R214.2
unnamed: Q187.3, R219.2
unnamed: Q187.6, R220.1
unnamed: Q188.2, Q188.5, Q197.2, Q197.5, R215.1, R216.2
unnamed: Q188.3, R221.2
unnamed: Q188.6, R222.1
unnamed: Q189.2, Q189.5, R217.1, R218.2
unnamed: Q189.3, R223.2
unnamed: Q189.6, R224.1
unnamed: Q190.2, Q190.5, R219.1, R220.2
unnamed: Q190.3, R225.2
unnamed: Q190.6, R226.1
unnamed: Q191.2, Q191.5, R221.1, R222.2
unnamed: Q191.3, R227.2
unnamed: Q191.6, R228.1
unnamed: Q192.2, Q192.5, R223.1, R224.2
unnamed: Q192.3, Q195.4
unnamed: Q192.6, Q195.1
unnamed: Q193.2, Q193.5, R225.1, R226.2
unnamed: Q193.3, Q196.4
unnamed: Q193.6, Q196.1
unnamed: Q194.2, Q194.5, R227.1, R228.2
unnamed: Q194.3, Q197.4
unnamed: Q194.6, Q197.1
unnamed: Q195.3, R229.2
unnamed: Q195.6, R230.1
unnamed: Q196.3, R231.2
unnamed: Q196.6, R232.1
unnamed: Q197.3, R233.2
unnamed: Q197.6, R234.1
unnamed: Q198.3, Q201.4
unnamed: Q198.6, Q201.1
unnamed: Q199.3, Q202.4
unnamed: Q199.6, Q202.1
unnamed: Q200.3, Q203.4
unnamed: Q200.6, Q203.1
unnamed: Q201.3, R235.2
unnamed: Q201.6, R236.1
unnamed: Q202.3, R237.2
unnamed: Q202.6, R238.1
unnamed: Q203.3, R239.2
unnamed: Q203.6, R240.1
unnamed: Q204.2, Q204.5, R242.1, R244.2
unnamed: Q204.3, R241.2
unnamed: Q204.6, R243.1
unnamed: Q205.1, Q206.6
unnamed: Q205.3, Q206.3, R242.2
unnamed: Q205.6, R244.1
unnamed: Q207.2, Q207.5, R246.1, R248.2
unnamed: Q207.3, R245.2
unnamed: Q207.6, R247.1
unnamed: Q208.1, Q209.6
unnamed: Q208.3, Q209.3, R246.2
unnamed: Q208.6, R248.1
unnamed: Q210.2, Q210.5, R250.1, R252.2
unnamed: Q210.3, R249.2
unnamed: Q210.6, R251.1
unnamed: Q211.1, Q212.6
unnamed: Q211.3, Q212.3, R250.2
unnamed: Q211.6, R252.1
unnamed: Q213.2, Q213.5, R254.1, R256.2
unnamed: Q213.3, R253.2
unnamed: Q213.6, R255.1
unnamed: Q214.1, Q215.6
unnamed: Q214.3, Q215.3, R254.2
unnamed: Q214.6, R256.1
unnamed: Q216.2, Q216.5, R258.1, R260.2
unnamed: Q216.3, R257.2
unnamed: Q216.6, R259.1
unnamed: Q217.1, Q218.6
unnamed: Q217.3, Q218.3, R258.2
unnamed: Q217.6, R260.1
unnamed: Q219.2, Q219.5, R262.1, R264.2
unnamed: Q219.3, R261.2
unnamed: Q219.6, R263.1
unnamed: Q220.1, Q221.6
unnamed: Q220.3, Q221.3, R262.2
unnamed: Q220.6, R264.1
unnamed: Q222.2, Q222.5, R266.1, R268.2
unnamed: Q222.3, R265.2
unnamed: Q222.6, R267.1
unnamed: Q223.1, Q224.6
unnamed: Q223.3, Q224.3, R266.2
unnamed: Q223.6, R268.1
unnamed: Q225.2, Q225.5, R270.1, R272.2
unnamed: Q225.3, R269.2
unnamed: Q225.6, R271.1
unnamed: Q226.1, Q227.6
unnamed: Q226.3, Q227.3, R270.2
unnamed: Q226.6, R272.1
unnamed: Q228.2, Q228.5, R274.1, R276.2
unnamed: Q228.3, R273.2
unnamed: Q228.6, R275.1
unnamed: Q229.1, Q230.6
unnamed: Q229.3, Q230.3, R274.2
unnamed: Q229.6, R276.1
unnamed: Q231.2, Q231.5, R278.1, R280.2
unnamed: Q231.3, R277.2
unnamed: Q231.6, R279.1
unnamed: Q232.3, R278.2
unnamed: Q232.4, Q233.3
unnamed: Q232.6, Q233.6, R280.1
unnamed: Q234.2, Q234.5, R282.1, R284.2
unnamed: Q234.3, R281.2
unnamed: Q234.6, R283.1
unnamed: Q235.3, R282.2
unnamed: Q235.4, Q236.3
unnamed: Q235.6, Q236.6, R284.1
unnamed: Q237.2, Q237.5, R286.1, R288.2
unnamed: Q237.3, R285.2
unnamed: Q237.6, R287.1
unnamed: Q238.3, R286.2
unnamed: Q238.4, Q239.3
unnamed: Q238.6, Q239.6, R288.1
unnamed: Q240.2, Q240.5, R290.1, R292.2
unnamed: Q240.3, R289.2
unnamed: Q240.6, R291.1
unnamed: Q241.3, R290.2
unnamed: Q241.4, Q242.3
unnamed: Q241.6, Q242.6, R292.1
unnamed: Q243.2, Q243.5, R294.1, R296.2
unnamed: Q243.3, R293.2
unnamed: Q243.6, R295.1
unnamed: Q244.3, R294.2
unnamed: Q244.4, Q245.3
unnamed: Q244.6, Q245.6, R296.1
unnamed: Q246.2, Q246.5, R298.1, R300.2
unnamed: Q246.3, R297.2
unnamed: Q246.6, R299.1
unnamed: Q247.3, R298.2
unnamed: Q247.4, Q248.3
unnamed: Q247.6, Q248.6, R300.1
unnamed: Q249.2, Q249.5, R302.1, R304.2
unnamed: Q249.3, R301.2
unnamed: Q249.6, R303.1
unnamed: Q250.3, R302.2
unnamed: Q250.4, Q251.3
unnamed: Q250.6, Q251.6, R304.1
unnamed: Q252.2, Q252.5, R306.1, R308.2
unnamed: Q252.3, R305.2
unnamed: Q252.6, R307.1
unnamed: Q253.3, R306.2
unnamed: Q253.4, Q254.3
unnamed: Q253.6, Q254.6, R308.1
unnamed: Q255.2, Q255.5, R310.1, R312.2
unnamed: Q255.3, R309.2
unnamed: Q255.6, R311.1
unnamed: Q256.3, R310.2
unnamed: Q256.4, Q257.3
unnamed: Q256.6, Q257.6, R312.1
unnamed: Q258.2, Q258.5, R315.1, R316.2
unnamed: Q258.3, Q259.3, R313.2
unnamed: Q258.6, Q259.6, R314.1
unnamed: Q260.3, R315.2
unnamed: Q260.6, R316.1
unnamed: Q261.2, Q261.5, R319.1, R320.2
unnamed: Q261.3, Q262.3, R317.2
unnamed: Q261.6, Q262.6, R318.1
unnamed: Q263.3, R319.2
unnamed: Q263.6, R320.1
unnamed: Q264.2, Q264.5, R323.1, R324.2
unnamed: Q264.3, Q265.3, R321.2
unnamed: Q264.6, Q265.6, R322.1
unnamed: Q266.3, R323.2
unnamed: Q266.6, R324.1
unnamed: Q267.2, Q267.5, R327.1, R328.2
unnamed: Q267.3, Q268.3, R325.2
unnamed: Q267.6, Q268.6, R326.1
unnamed: Q269.3, R327.2
unnamed: Q269.6, R328.1
unnamed: Q270.2, Q270.5, R331.1, R332.2
unnamed: Q270.3, Q271.3, R329.2
unnamed: Q270.6, Q271.6, R330.1
unnamed: Q272.3, R331.2
unnamed: Q272.6, R332.1
unnamed: Q273.2, Q273.5, R335.1, R336.2
unnamed: Q273.3, Q274.3, R333.2
unnamed: Q273.6, Q274.6, R334.1
unnamed: Q275.3, R335.2
unnamed: Q275.6, R336.1
unnamed: Q276.2, Q276.5, R339.1, R340.2
unnamed: Q276.3, Q277.3, R337.2
unnamed: Q276.6, Q277.6, R338.1
unnamed: Q278.3, R339.2
unnamed: Q278.6, R340.1
unnamed: Q279.2, Q279.5, R343.1, R344.2
unnamed: Q279.3, Q280.3, R341.2
unnamed: Q279.6, Q280.6, R342.1
unnamed: Q281.3, R343.2
unnamed: Q281.6, R344.1
unnamed: Q282.2, Q282.5, R347.1, R348.2
unnamed: Q282.3, Q283.3, R345.2
unnamed: Q282.6, Q283.6, R346.1
unnamed: Q284.3, R347.2
unnamed: Q284.6, R348.1
unnamed: Q285.2, Q285.5, R350.1, R352.2
unnamed: Q285.3, R349.2
unnamed: Q285.6, R351.1
unnamed: Q286.3, Q287.3, R350.2
unnamed: Q286.6, Q287.6, R352.1
unnamed: Q288.2, Q288.5, R354.1, R356.2
unnamed: Q288.3, R353.2
unnamed: Q288.6, R355.1
unnamed: Q289.3, Q290.3, R354.2
unnamed: Q289.6, Q290.6, R356.1
unnamed: Q291.2, Q291.5, R358.1, R360.2
unnamed: Q291.3, R357.2
unnamed: Q291.6, R359.1
unnamed: Q292.3, Q293.3, R358.2
unnamed: Q292.6, Q293.6, R360.1
unnamed: Q294.2, Q294.5, R362.1, R364.2
unnamed: Q294.3, R361.2
unnamed: Q294.6, R363.1
unnamed: Q295.3, Q296.3, R362.2
unnamed: Q295.6, Q296.6, R364.1
unnamed: Q297.2, Q297.5, R366.1, R368.2
unnamed: Q297.3, R365.2
unnamed: Q297.6, R367.1
unnamed: Q298.3, Q299.3, R366.2
unnamed: Q298.6, Q299.6, R368.1
unnamed: Q300.2, Q300.5, R370.1, R372.2
unnamed: Q300.3, R369.2
unnamed: Q300.6, R371.1
unnamed: Q301.3, Q302.3, R370.2
unnamed: Q301.6, Q302.6, R372.1
unnamed: Q303.2, Q303.5, R374.1, R376.2
unnamed: Q303.3, R373.2
unnamed: Q303.6, R375.1
unnamed: Q304.3, Q305.3, R374.2
unnamed: Q304.6, Q305.6, R376.1
unnamed: Q306.2, Q306.5, R378.1, R380.2
unnamed: Q306.3, R377.2
unnamed: Q306.6, R379.1
unnamed: Q307.3, Q308.3, R378.2
unnamed: Q307.6, Q308.6, R380.1
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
